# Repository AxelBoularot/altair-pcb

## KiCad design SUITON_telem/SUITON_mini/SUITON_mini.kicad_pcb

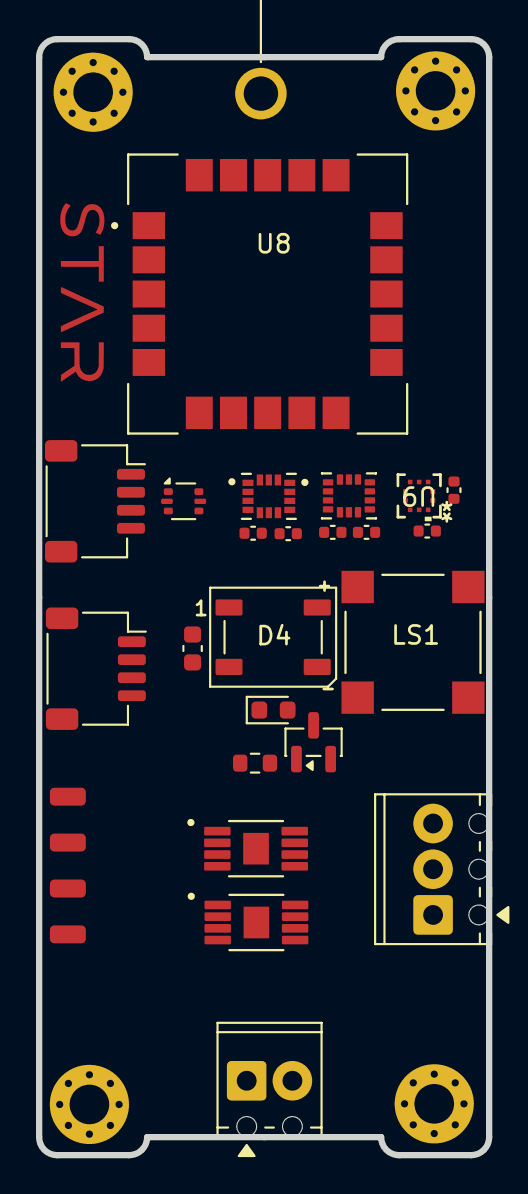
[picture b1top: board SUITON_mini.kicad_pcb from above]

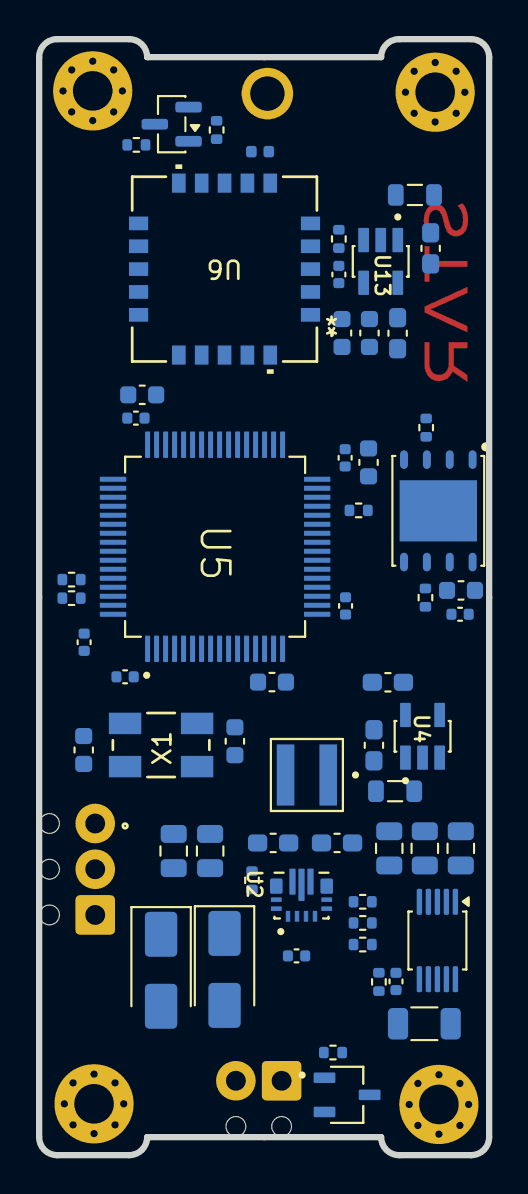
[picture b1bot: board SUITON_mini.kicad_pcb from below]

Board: 2 copper layers, 25.0 x 62.0 mm, 91 parts (59 on the bottom side), 61 nets, no tracks yet.

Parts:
C1, C2: 10uF; C_0805_2012Metric
C3, C5: 10uF; C_0603_1608Metric_Pad1.08x0.95mm_HandSolder
C4, C9, C13, C14, C16, C17, C18, C19, C22, C29, C30, C31, C33, C34: 100nF; C_0402_1005Metric
C6, C7, C8: 22uF; C_0805_2012Metric
C10, C11, C15, C26: 1uF; C_0603_1608Metric_Pad1.08x0.95mm_HandSolder
C12: 100n; C_0402_1005Metric
C20, C24, C39: 100nF; C_0603_1608Metric
C23, C37, C38: 2.2uF; C_0603_1608Metric
C25: 10uF; C_0603_1608Metric
C28, C32: 12pF; C_0603_1608Metric
D4: WS2812B; LED_WS2812B_PLCC4_5.0x5.0mm_P3.2mm
D5: 1N4148; D_0603_1608Metric
D8, D9: SS34; D_SMA
E1: ANT-868-JJB-RA; XDCR_ANT-868-JJB-RA
FB1, FB2: FerriteBead; L_0805_2012Metric
H1, H2, H3, H4: MountingHole_Pad; MountingHole_2.2mm_M2_Pad_Via
J1: Conn_01x02_Pin; TerminalBlock_Phoenix_MPT-0,5-2-2.54_1x02_P2.54mm_Horizontal
J2, J2#2: Conn_01x04_Pin; JST_SH_SM04B-SRSS-TB_1x04-1MP_P1.00mm_Horizontal
J5: Conn_01x03_Pin; TerminalBlock_Phoenix_MPT-0,5-3-2.54_1x03_P2.54mm_Horizontal
J6, J7, J8, J9: Conn_01x01_Pin; SolderWirePad_1x01_SMD_1x2mm
L2: 330n; L_0402_1005Metric
L3: XFL4020-152MEC; IND_XFL4020-152MEC
LS1: CMT-7525-80-SMT-TR; XDCR_CMT-7525-80-SMT-TR
Q2: AO3407A; SOT95P280X125-3N
Q3, Q4: BSS138; SOT-23
R1: 20m; R_1206_3216Metric
R4, R29, R30, R31, R37, R38: 10kΩ; R_0402_1005Metric
R5: 100kΩ; R_0402_1005Metric
R6: 680kΩ; R_0402_1005Metric
R7: 130kΩ; R_0402_1005Metric
R8, R9, R21, R22: 10k; R_0402_1005Metric
R19: 10kΩ; R_0603_1608Metric
R20: 100k; R_0402_1005Metric
U1: W25Q128JVPIQ
U2: TPS63070RNMR; VREG_TPS63070RNMR
U3: INA226; TSSOP-10_3x3mm_P0.5mm
U4, U13: AP2112K-3.3TRG1; SOT95P285X140-5N
U5: STM32F405RGT6; QFP50P1200X1200X160-64N
U6: E22-900MM22S; E22-900MM22S_BYT
U7: ISM330DHCXTR; PQFN50P250X300X86-14N
U8: SAM-M10Q-00B; XCVR_SAM-M10Q-00B
U9: BMP581; QFN10_BMP581_BOS
U10: LSM6DSV320XTR; PQFN50P250X300X86-14N
U11: USBLC6-2P6; SOT-666
U12, U14: TPS1H200AQDGNRQ1; SOP65P490X110-9N
X1: ABM3B-8.000MHZ-10-1UT; XTAL4P_ABM3B_ABR

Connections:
+3.3V: R20.1, R21.1
+3V3: C9.2, C11.1, C13.2, C14.2, C16.2, C17.2, C18.1, C19.2, C22.2, C23.2, C29.1, C30.1, C31.1, C33.1, C34.1, C39.2, R8.1, R30.1, R31.1, R37.1, R38.1, U1.8 (VCC), U3.6 (VS), U4.5 (VOUT), U5.1 (VBAT), U5.13 (VDDA), U5.19 (VDD), U5.32 (VDD), U5.48 (VDD), U5.64 (VDD), U7.5 (VDD_IO), U7.8 (VDD), U8.2 (V_IO), U8.3 (V_BCKP), U8.17 (VCC), U9.1 (VDDIO), U9.10 (VDD), U10.5 (VDDIO), U10.8 (VDD)
+3V3_radio: C24.2, C25.2, C26.1, U6.1 (VCC), U13.5 (VOUT)
+5V: C5.1, C6.1, C7.1, C8.1, C20.2, D4.1 (VDD), D5.1 (K), FB1.1, FB2.1, LS1.P, R5.1, R6.1, U2.7_8 (VOUT)
+5V_USB: D9.2 (A), J2#2.1, U11.5 (VBUS)
/MCU/BOOT: R29.1, U5.60 (BOOT0)
/MCU/OSC_IN: C28.1, U5.5 (PH0/OSC_IN), X1.1
/MCU/OSC_OUT: C32.1, U5.6 (PH1/OSC_OUT), X1.3
/MCU/USB_D+: U5.45 (PA12), U11.4 (I/O2)
/MCU/USB_D-: U5.44 (PA11), U11.6 (I/O1)
/Memory/ANT: E1.1, L2.1, U6.6 (ANT)
/Memory/RX_EN: Q4.3 (D), R21.2, U6.10 (RXEN)
/Memory/TX_EN: Q4.1 (G), R22.2, U6.9 (TXEN), U6.19 (DIO2)
Alert: R8.2, U3.3 (~Alert), U5.15 (PA1/USART2_RTS)
BUZZER: Q3.1 (G), R19.2, U5.14 (PA0/WKUP)
CS_BMP: U5.53 (PC12), U9.6 (CSB)
CS_MEM: U1.1 (CS), U5.33 (PB12)
DIO1_RF: U5.57 (PB5), U6.20 (DIO1)
EXTINT_SAM: U5.25 (PC5), U8.19 (EXTINT)
GND: C1.2, C2.2, C3.2, C4.2, C5.2, C6.2, C7.2, C8.2, C9.1, C10.2, C11.2, C12.2, C13.1, C14.1, C15.2, C16.1, C17.1, C18.2, C19.1, C20.1, C22.1, C23.1, C24.1, C25.1, C26.2, C28.2, C29.2, C30.2, C31.2, C32.2, C33.2, C34.2, C37.2, C38.2, C39.1, D4.3 (VSS), H1.1 (1_1), H2.1 (1_1), H3.1 (1_1), H4.1 (1_1), J1.1, J2#2.4, J5.1, L2.2, Q3.2 (S), Q4.2 (S), R7.2, R9.1, R19.1, R22.1, R29.2, U1.4 (GND), U1.9 (GND), U2.4 (GND), U2.6 (FB2), U2.10 (PGND), U2.15 (VSEL), U3.1 (A1), U3.2 (A0), U3.7 (GND), U4.2 (GND), U5.12 (VSSA), U5.18 (VSS), U5.63 (VSS), U6.2 (GND), U6.7 (GND), U6.16 (GND), U7.2 (SDX), U7.3 (SCX), U7.6 (GND), U7.7 (GND), U8.1 (GND), U8.4 (GND), U8.5 (GND), U8.6 (GND), U8.10 (GND), U8.11 (GND), U8.15 (GND), U8.16 (GND), U8.20 (GND), U9.3 (VSS), U9.8 (VSS), U9.9 (VSS), U10.2 (SDX), U10.3 (SCX), U10.6 (GND), U10.7 (GND), U11.2 (GND), U12.5 (DELAY), U12.6 (GND), U12.9 (EP), U13.2 (GND), U14.5 (DELAY), U14.6 (GND), U14.9 (EP), X1.2, X1.4
INT1_IMU1: U5.8 (PC0), U7.4 (INT1)
INT1_IMU2: U5.51 (PC10), U10.4 (INT1)
INT2_IMU1: U5.9 (PC1), U7.9 (INT2)
INT2_IMU2: U5.52 (PC11), U10.9 (INT2)
INT_BMP: U5.54 (PD2), U9.7 (INT)
LED: D4.4 (DIN), U5.16 (PA2/USART2_TX)
MISO_SPI1: U5.22 (PA6/SPI1_MISO), U7.1 (SDO/SA0), U10.1 (SDO/TA0)
MISO_SPI2: U1.2 (DO(IO1)), U5.35 (PB14), U6.12 (MISO)
MOSI_SPI1: U5.23 (PA7/SPI1_MOSI), U7.14 (SDA), U9.4 (SDI), U9.5 (SDO), U10.14 (SDA)
MOSI_SPI2: U1.5 (DI(IO0)), U5.36 (PB15), U6.13 (MOSI)
unnamed: D5.2 (A), LS1.N, Q3.3 (D)
unnamed: D8.2 (A), R1.1, U3.9 (Vin-)
unnamed: C1.1, C2.1, C3.1, D8.1 (K), D9.1 (K), R4.2, U2.12_13 (VIN)
unnamed: J1.2, Q2.2
unnamed: J2#2.2, U11.1 (I/O1)
unnamed: J2#2.3, U11.3 (I/O2)
unnamed: Q2.1, R9.2
unnamed: R31.2, U1.7 (HOLD/RESET(IO3))
unnamed: R30.2, U1.3 (/WP(IO2))
unnamed: R4.1, U2.1 (PS/SYNC), U2.14 (EN)
unnamed: R6.2, R7.1, U2.5 (FB)
unnamed: L3.2, U2.11 (L1)
unnamed: L3.1, U2.9 (L2)
unnamed: R5.2, U2.2 (PG)
unnamed: C4.1, U2.3 (VAUX)
unnamed: C10.1, FB1.2, U4.1 (VIN)
unnamed: C38.1, U5.31 (VCAP_1)
unnamed: C37.1, U5.47 (VCAP_2)
unnamed: C15.1, FB2.2, U13.1 (VIN)
PYRO1out: J5.3, U14.7 (OUT)
PYRO2out: J5.2, U12.7 (OUT)
RESET_RF: C12.1, R20.2, U5.61 (PB8), U6.3 (NRST)
RESET_SAM: U5.41 (PA8), U8.18 (~RESET)
SAFEBOOT_SAM: U5.50 (PA15), U8.8 (~SAFEBOOT)
SCLK_SPI1: U5.21 (PA5/SPI1_SCK), U7.13 (SCL), U9.2 (SCK), U10.13 (SCL)
SCLK_SPI2: U1.6 (CLK), U5.34 (PB13)
SCL_I2C1: R37.2, U3.5 (SCL), U5.62 (PB9)
SDA_I2C1: R38.2, U3.4 (SDA), U5.29 (PB10)
UART1_RX: U5.43 (PA10), U8.13 (TXD)
UART1_TX: U5.42 (PA9), U8.14 (RXD)
VCC: Q2.3, R1.2, U3.8 (Vbus), U3.10 (Vin+), U12.8 (VS), U14.8 (VS)
